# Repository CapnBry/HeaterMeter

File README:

This is the source code respository for the HeaterMeter and LinkMeter BBQ grill controllers. Documentation can be found in the wiki:
https://github.com/CapnBry/HeaterMeter/wiki

+-----+ +-----+ +------+
|Probe| |Probe| |Blower|
+-----+ +-----+ +------+
     |       |        |    2.5mm jacks
A +-------------+     |
V | HeaterMeter |-----/    (arduino/heatermeter)
R +-------------+
========|===============   Serial UART
  +------------------+
  | +------------+ |
O | | linkmeterd | |      (openwrt/package/linkmeter)
p | +------------+ |
e |       |        |      /var/run/linkmeter.sock
n |    +------+    |
W |    | luci |    |      LUA in-process
r |   +--------+   |
t |   | uhttpd |   |
  |   +--------+   |
  +-----------------+
  
Source Layout
3d/* - 3D printed parts source files
openwrt/* - Files you'd push to your router for LinkMeter
arduino/* - AVR source code for upload to your Arduino board
eagle/* - Hardware schematics and board files
pebble/* - Source to the Pebble app
tools/* - Miscellaneous scripts and .NET apps

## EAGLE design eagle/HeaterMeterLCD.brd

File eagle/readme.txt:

KiCad Files for HeaterMeter PCBs
Base - HeaterMeter Base Board (v4.3.5)
LCD - HeaterMeter v4.3 LCD and Button backpack board (v4.3.5)

-- Obsolete EAGLE files or of Limited Purpose --
HeaterMeterPI.brd / sch / png - HeaterMeter v4 board and schematic for standalone or RaspberryPi (up to v4.3.4)
HeaterMeterLCD.brd / sch / png - HeaterMeter v4.3 LCD and Button backpack board (up to v4.3.4)
RfAddon.brd / sch - HeaterMeter v4.2.4 RF addon board needed if lmremote / IT+ reception is desired
LMRemote.sch - Example RF Remote probe transmitter schematic (not used in v4.3)

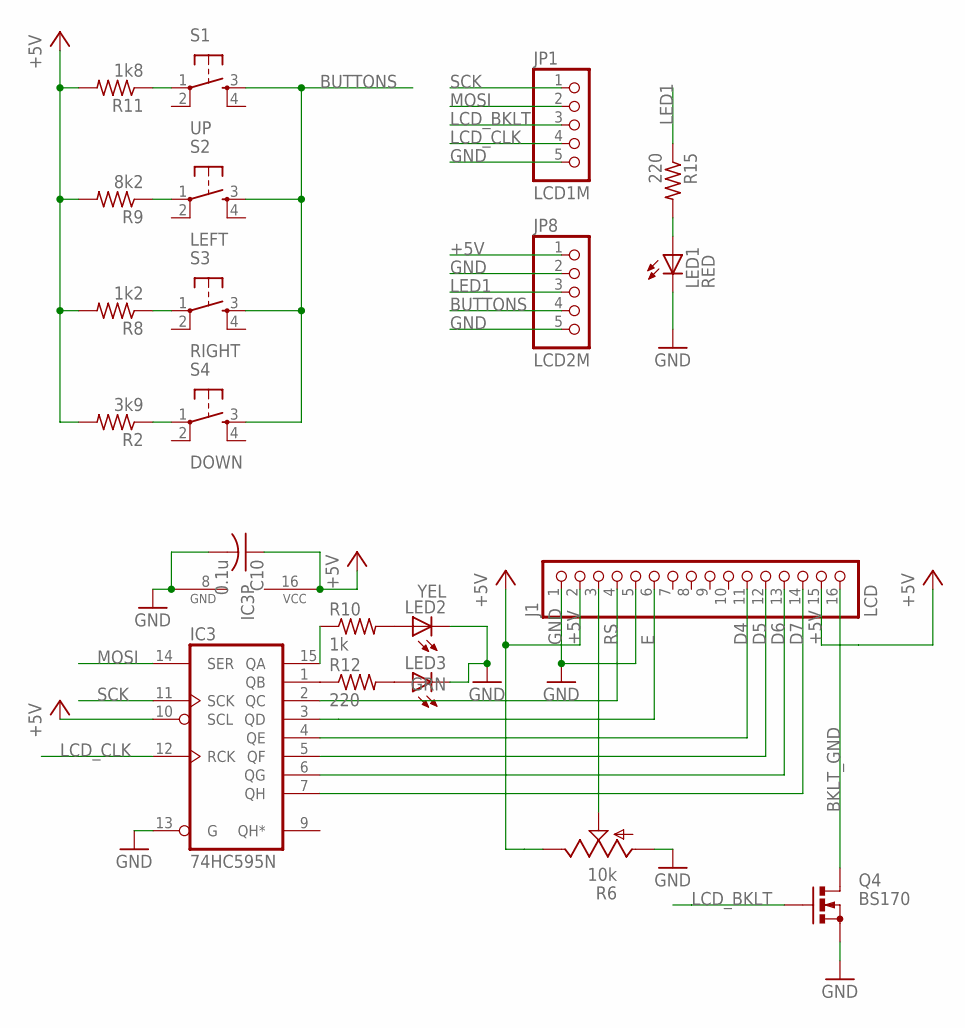
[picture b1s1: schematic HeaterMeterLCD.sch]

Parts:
C10: 0.1u; C025-025X050
IC3: 74HC595N; DIL16
J1: LCD; 1X16
JP1: LCD1M; 1X05
JP8: LCD2M; 1X05
LED1: RED; LED3MM
LED2: YEL; LED3MM
LED3: GRN; LED3MM
Q4: BS170; SOT54E
R2: 3k9; 0204/7
R6: 10k; POT-CT6-SIDE
R8: 1k2; 0204/7
R9: 8k2; 0204/7
R10: 1k; 0204/7
R11: 1k8; 0204/7
R12, R15: 220; 0204/7
S1: UP; TACT-OMRON-12MM
S2: LEFT; TACT-OMRON-12MM
S3: RIGHT; TACT-OMRON-12MM
S4: DOWN; TACT-OMRON-12MM

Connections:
+5V: C10.1, IC3.10 (SCL), IC3.16 (VCC), J1.2, J1.15, JP8.1, R2.2, R6.E, R8.2, R9.2, R11.2
BKLT_GND: J1.16, Q4.D
BUTTONS: JP8.4, S1.3, S2.3, S3.3, S4.3
D4: IC3.4 (QE), J1.11
D5: IC3.5 (QF), J1.12
D6: IC3.6 (QG), J1.13
D7: IC3.7 (QH), J1.14
E: IC3.3 (QD), J1.6
GND: C10.2, IC3.8 (GND), IC3.13 (G), J1.1, J1.5, JP1.5, JP8.2, JP8.5, LED1.K (C), LED2.K (C), LED3.K (C), Q4.S, R6.A
LCD_BKLT: JP1.3, Q4.G
LCD_CLK: IC3.12 (RCK), JP1.4
LED1: JP8.3, R15.1
MOSI: IC3.14 (SER), JP1.2
unnamed: R2.1, S4.1
unnamed: R11.1, S1.1
unnamed: J1.3, R6.S
unnamed: R9.1, S2.1
unnamed: LED2.A, R10.2
unnamed: LED1.A, R15.2
unnamed: R8.1, S3.1
unnamed: IC3.15 (QA), R10.1
unnamed: IC3.1 (QB), R12.1
unnamed: LED3.A, R12.2
RS: IC3.2 (QC), J1.4
SCK: IC3.11 (SCK), JP1.1

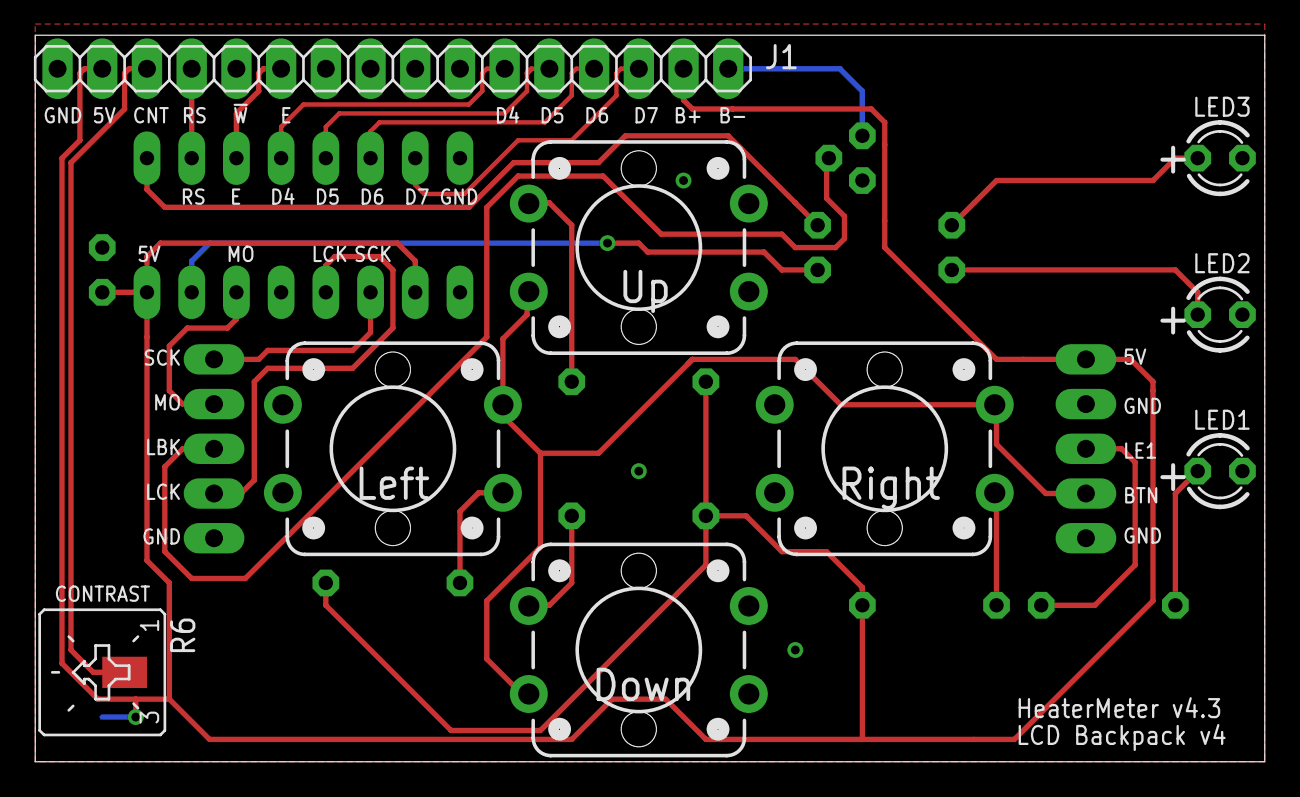
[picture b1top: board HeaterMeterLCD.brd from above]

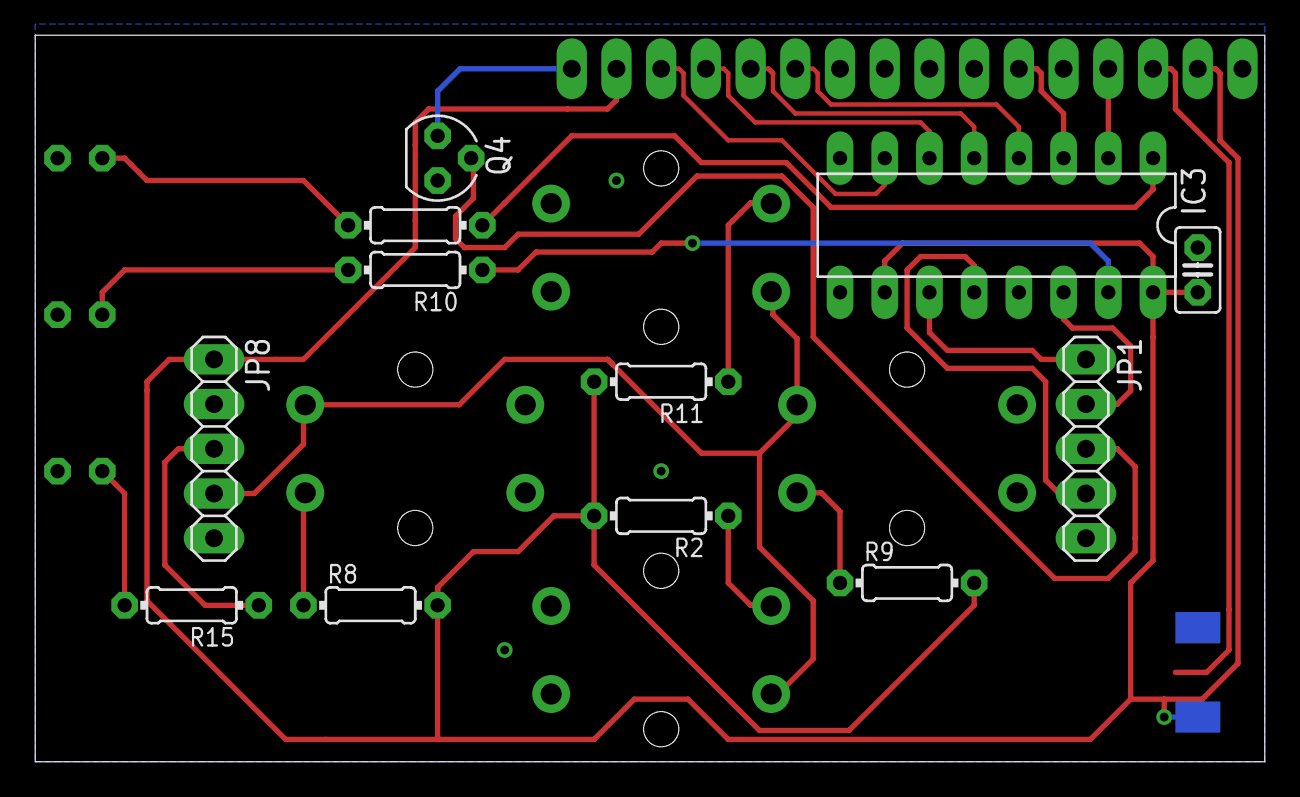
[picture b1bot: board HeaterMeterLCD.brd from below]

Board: 2 copper layers, 69.8 x 41.3 mm, 21 parts (12 on the bottom side), 25 nets.

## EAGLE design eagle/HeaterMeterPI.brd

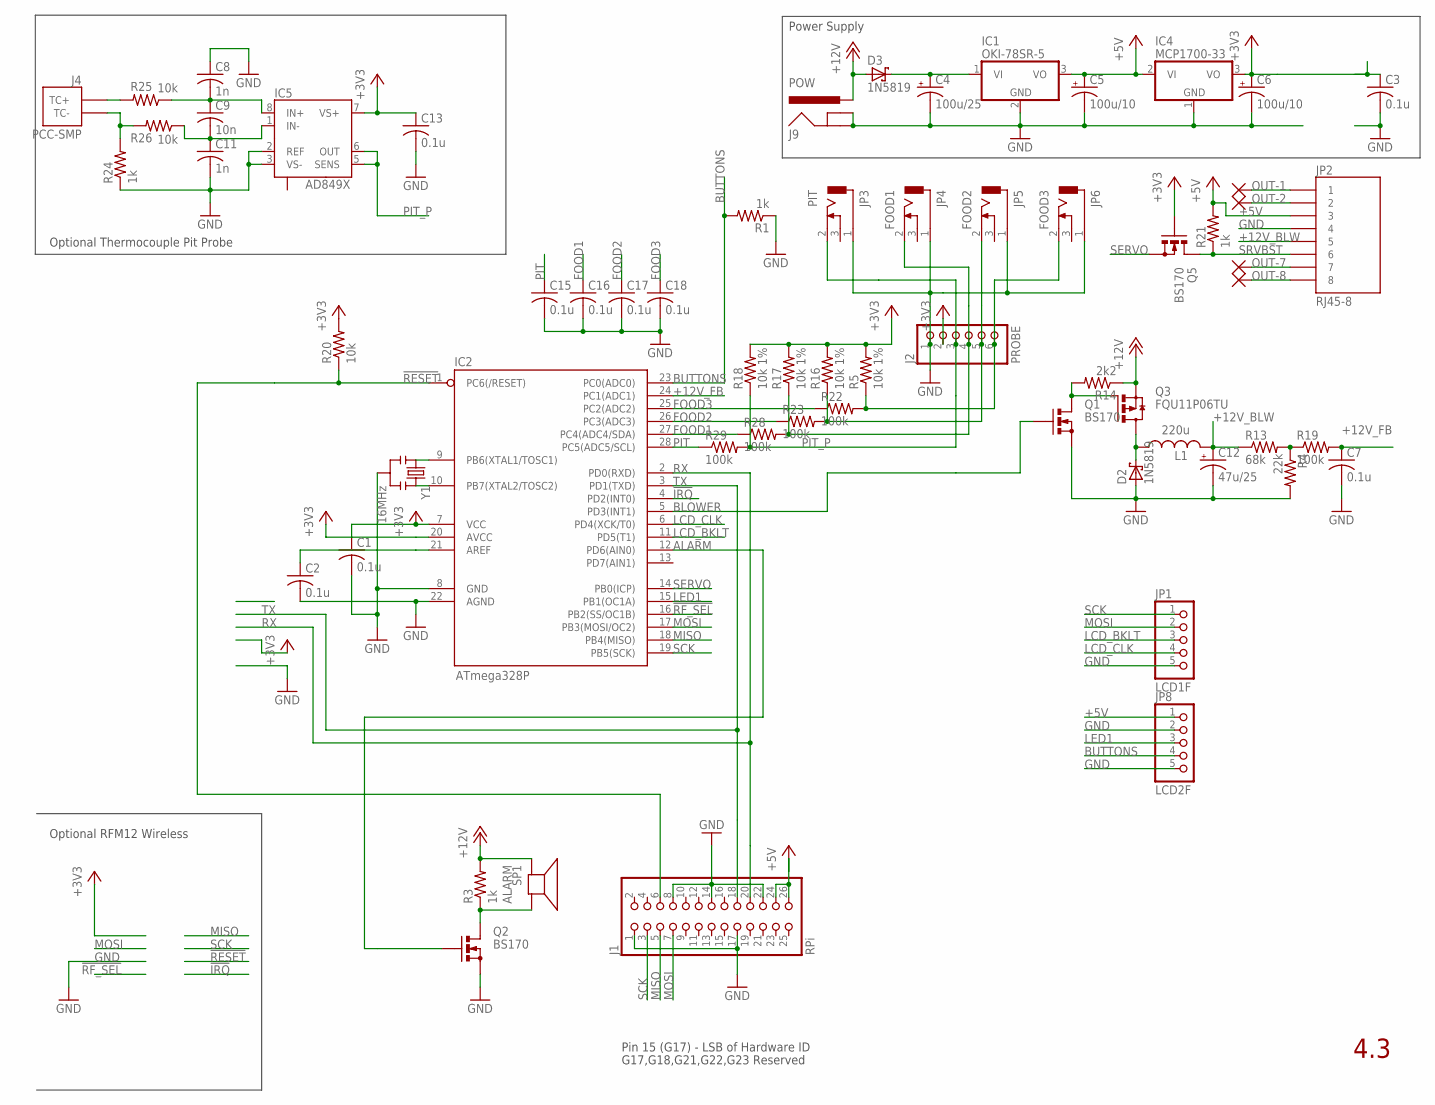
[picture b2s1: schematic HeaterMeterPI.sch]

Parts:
C1, C2, C3, C7, C15, C16, C17, C18: 0.1u; C025-025X050
C4: 100u/25; E2,5-6
C5, C6: 100u/10; E2,5-5
C8, C11: 1n; C0805
C9: 10n; C0805
C12: 47u/25; E2,5-5
C13: 0.1u; C0805
D2, D3: 1N5819; DO41-7
IC1: OKI-78SR-5; TO220HMURATA
IC2: ATmega328P; DIL28-3
IC4: MCP1700-33; TO92
IC5: AD849X; MSOP8
J1: RPi; 2X13
J2: PROBE; 1X06
J4: PCC-SMP
J9: POW; BARREL-2.1
JP1: LCD1F; 1X05
JP2: RJ45-8; RJ45-8-1H
JP3: PIT; CUI-MJ-2508
JP4: FOOD1; CUI-MJ-2508
JP5: FOOD2; CUI-MJ-2508
JP6: FOOD3; CUI-MJ-2508
JP8: LCD2F; 1X05
L1: 220u; E5-9
Q1, Q2, Q5: BS170; SOT54E
Q3: FQU11P06TU; TO251
R1, R3, R21: 1k; 0204/7
R4: 22k; 0204/7
R5, R16, R17, R18: 10k 1%; 0207/2V
R13: 68k; 0204/7
R14: 2k2; 0204/7
R19: 100k; 0204/7
R20: 10k; 0204/7
R22, R23, R28, R29: 100k; 0207/2V
R24: 1k; R0805
R25, R26: 10k; R0805
SP1: ALARM; AL11P
U$1, U$2, U$3, U$4: THROUGH-HOLE; PAD-032
Y1: 16MHz; RESONATOR-PTH

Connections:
!IRQ: IC2.4 (PD2(INT0))
!RESET: IC2.1 (PC6(/RESET)), J1.6, R20.1
!RF_SEL: IC2.16 (PB2(SS/OC1B))
+3V3: C1.1, C3.1, C6.+, C13.1, IC2.7 (VCC), IC2.20 (AVCC), IC4.3 (VO), IC5.7 (VS+), J2.2, Q5.G, R5.2, R16.2, R17.2, R18.2, R20.2
+5V: C5.+, IC1.3 (VO), IC4.2 (VI), J1.24, J1.26, JP2.3, JP8.1, R21.2
+12V: D3.A, J9.PWR, Q3.3 (S), R3.2, R14.1, SP1.+
+12V_BLW: C12.+, JP2.5, L1.NEG (2), R13.1
+12V_FB: C7.1, IC2.24 (PC1(ADC1)), R19.2
ALARM: IC2.12 (PD6(AIN0)), Q2.G
BLOWER: IC2.5 (PD3(INT1)), Q1.G
BUTTONS: IC2.23 (PC0(ADC0)), JP8.4, R1.2
FOOD1: C16.1, IC2.27 (PC4(ADC4/SDA)), R28.1
FOOD1_P: J2.4, JP4.2, R17.1, R28.2
FOOD2: C17.1, IC2.26 (PC3(ADC3)), R23.1
FOOD2_P: J2.5, JP5.2, R16.1, R23.2
FOOD3: C18.1, IC2.25 (PC2(ADC2)), R22.1
FOOD3_P: J2.6, JP6.2, R5.1, R22.2
GND: C1.2, C2.2, C3.2, C4.-, C5.-, C6.-, C7.2, C8.1, C11.2, C12.-, C13.2, C15.2, C16.2, C17.2, C18.2, D2.A, IC1.2 (GND), IC2.8 (GND), IC2.22 (AGND), IC4.1 (GND), IC5.2 (REF), IC5.3 (VS-), J1.1, J1.8, J1.14, J1.17, J1.22, J2.1, J9.GND, J9.GNDBREAK, JP1.5, JP2.4, JP3.1, JP4.1, JP5.1, JP6.1, JP8.2, JP8.5, Q1.S, Q2.S, R1.1, R4.2, R24.1, Y1.2
LCD_BKLT: IC2.11 (PD5(T1)), JP1.3
LCD_CLK: IC2.6 (PD4(XCK/T0)), JP1.4
LED1: IC2.15 (PB1(OC1A)), JP8.3
MISO: IC2.18 (PB4(MISO)), J1.5
MOSI: IC2.17 (PB3(MOSI/OC2)), J1.7, JP1.2
unnamed: Q1.D, Q3.1 (G), R14.2
unnamed: C2.1, IC2.21 (AREF)
unnamed: D2.C, L1.POS (1), Q3.2@1 (D), Q3.2@2 (D)
unnamed: R4.1, R13.2, R19.1
unnamed: Q2.D, R3.1, SP1.-
unnamed: IC2.10 (PB7(XTAL2/TOSC2)), Y1.3
unnamed: IC2.9 (PB6(XTAL1/TOSC1)), Y1.1
unnamed: J4.TC+, R25.2
unnamed: J4.TC-, R24.2, R26.2
OUT-1: JP2.1, U$3.P
OUT-2: JP2.2, U$4.P
OUT-7: JP2.7, U$2.P
OUT-8: JP2.8, U$1.P
PIT: C15.1, IC2.28 (PC5(ADC5/SCL)), R29.1
PIT_P: IC5.5 (SENS), IC5.6 (OUT), J2.3, JP3.2, R18.1, R29.2
RX: IC2.2 (PD0(RXD)), J1.20
SCK: IC2.19 (PB5(SCK)), J1.3, JP1.1
SERVO: IC2.14 (PB0(ICP)), Q5.S
SRVBST: JP2.6, Q5.D, R21.1
TC+: C8.2, C9.1, IC5.8 (IN+), R25.1
TC-: C9.2, C11.1, IC5.1 (IN-), R26.1
TX: IC2.3 (PD1(TXD)), J1.18
VRM_IN: C4.+, D3.C, IC1.1 (VI)

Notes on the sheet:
Optional RFM12 Wireless
Power Supply
4.3
Optional Thermocouple Pit Probe
Pin 15 (G17) - LSB of Hardware ID
G17,G18,G21,G22,G23 Reserved

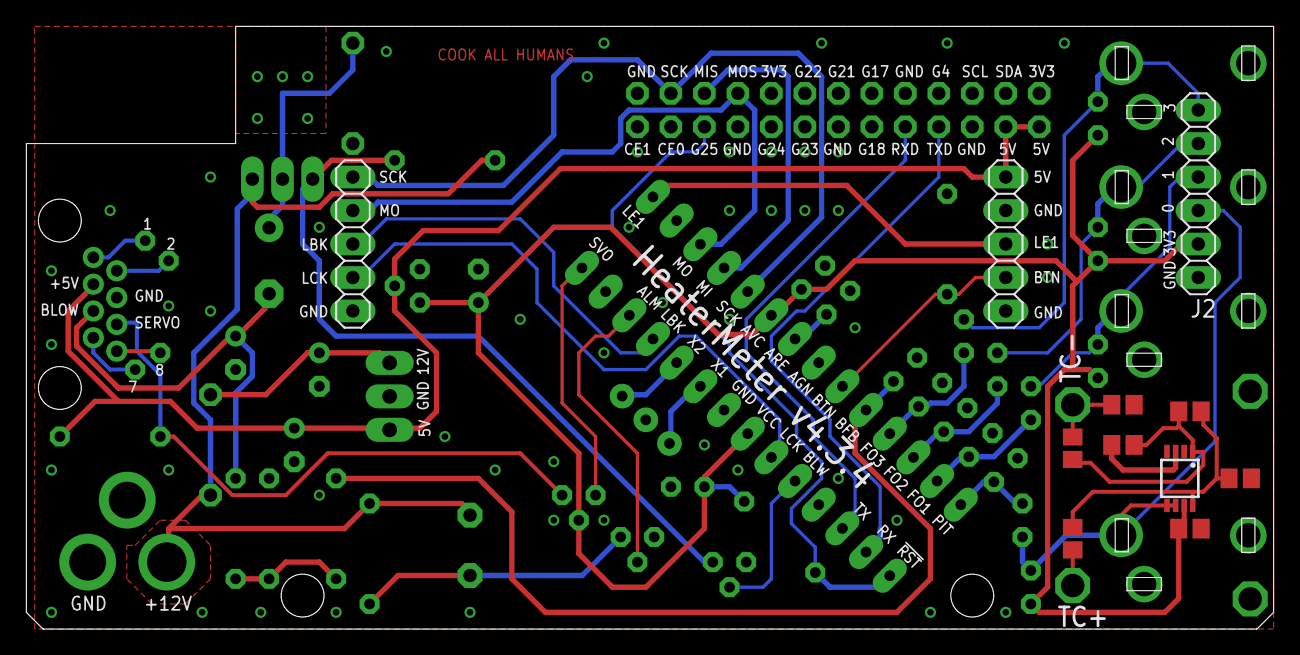
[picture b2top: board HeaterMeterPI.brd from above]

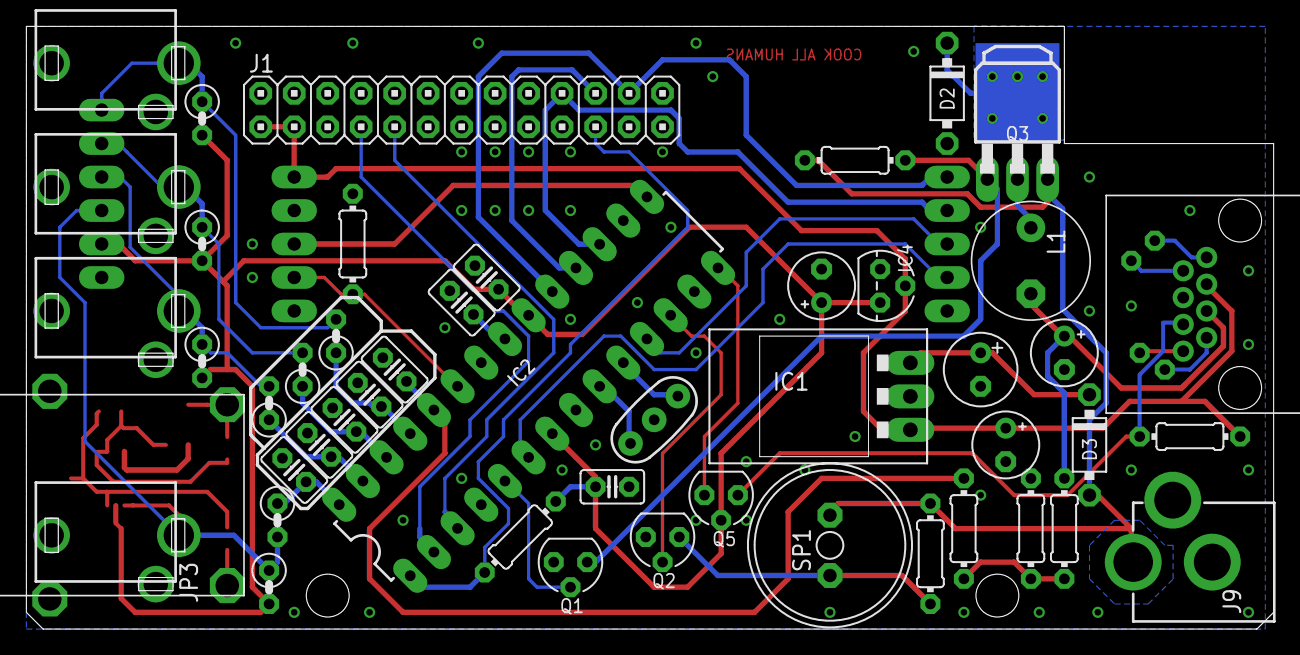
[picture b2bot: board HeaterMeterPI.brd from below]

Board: 2 copper layers, 94.6 x 45.7 mm, 63 parts (48 on the bottom side), 44 nets.

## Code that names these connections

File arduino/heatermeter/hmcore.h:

// HeaterMeter Copyright 2019 Bryan Mayland <bmayland@capnbry.net>
#ifndef __HMCORE_H__
#define __HMCORE_H__

#include "strings.h"

#define HEATERMETER_SERIAL 38400 // enable serial interface
#define HEATERMETER_RFM12  RF12_915MHZ  // enable RFM12B receiving (433MHZ|868MHZ|915MHZ)
#define PIEZO_HZ 4000             // enable piezo buzzer at this frequency
#if HM_BOARD_REV == 'A'
#define SHIFTREGLCD_NATIVE        // Use the native shift register instead of SPI (HM PCB <v3.2)
#endif

#include "ShiftRegLCD.h"
#include "serialxor.h"
#include "grillpid.h"
#include "hmmenus.h"

// Analog Pins
// Number in the comment is physical pin on ATMega328
#define PIN_PIT     5       // 28
#define PIN_FOOD1   4       // 27
#define PIN_FOOD2   3       // 26
#define PIN_AMB     2       // 25
//#define PIN_FFEEDBACK 1     // 24 (grillpid_conf.h)
#define PIN_BUTTONS 0       // 23
// Digital Output Pins
#define PIN_SERIALRX     0  // 2 Can not be changed
#define PIN_SERIALTX     1  // 3 Can not be changed
#define PIN_INTERRUPT    2  // 4
//#define PIN_BLOWER       3  // 5 (grillpid_conf.h)
#define PIN_LCD_CLK      4  // 6
#define PIN_LCD_BACKLGHT 5  // 11
//#define PIN_ALARM        6  // 12 (tone_4khz.h)
//#define PIN_SOFTRESET    7  // 13 DataFlash SS on WiShield, no longer used for reset
//#define PIN_SERVO        8  // 14 LCD_DATA on < HM PCB v3.2 (grillpid_conf.h)
#define PIN_WIRELESS_LED 9  // 15
#if !defined(PIN_SPI_SS)
#define PIN_SPI_SS      10  // 16
#define PIN_SPI_MOSI    11  // 17 Can not be changed
#define PIN_SPI_MISO    12  // 18 Can not be changed
#define PIN_SPI_SCK     13  // 19 Can not be changed
#endif

void hmcoreSetup(void);
void hmcoreLoop(void);

void eepromLoadConfig(unsigned char forceDefault);
void storePidMode();
void storeSetPoint(int sp);
void loadProbeName(unsigned char probeIndex);
void storeAndReportProbeOffset(unsigned char probeIndex, int offset);
void storeAndReportMaxFanSpeed(unsigned char maxFanSpeed);
void storeLcdBacklight(unsigned char lcdBacklight);
void reportLcdParameters(void);
void Debug_begin(void);
void publishLeds(void);
#define Debug_end Serial_nl
void silenceRingingAlarm(void);

#define LIDPARAM_OFFSET 0
#define LIDPARAM_DURATION 1
#define LIDPARAM_ACTIVE 2
void storeLidParam(unsigned char idx, int val);

extern GrillPid pid;
extern ShiftRegLCD lcd;

#endif /* __HMCORE_H__ */

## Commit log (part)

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2016-09-30 [wrt] Fix parted compilation
2016-09-30 [wrt] Remove spi-bcm2708, now included in platform modules.mk
2016-09-30 [wrt] Update from url patch updated to trunk luci
2016-09-30 [wrt] Remove dnsmasq add hostname
    Trunk now properly adds ipv4 and ipv6 hostname for "lan" network by default
2016-09-30 [wrt] Update luci-app-msmtp to 1.6.2 and match new luci base
2016-09-30 [lm] Allow use of 'auto' serial port, and make baud default to 38400 if not present
2016-09-30 [wrt] Refresh bcm2708 tweaks for Designated Driver and RPi 3
2016-09-30 [lm] Updated coefficients for Thermoworks ProSeries (0.4C-1.1C increase from 25C-150C)
2016-09-30 [wrt] Add 'reset config' to sysupgrade-url (now flashops) patch
2016-09-30 [lm] Updates for OpenWrt Designated Driver / Pi 3
    -- Linkmeter now uses its own config file instead of lucid
    -- Linkmeter is standaone, no longer requires lucid host process
    -- Still much to do but up and running
2016-10-01 [wrt] Simplify luci-app-msmtp Makefile to use luci.mk
2016-10-01 [wrt] LinkMeter depends on luci-base instad of luci, allows removal of firewall packages
2016-10-05 [3d] Remove mousears, add configurable body chamfer and walls now full 3mm
2016-10-11 [3d] USB pillars fix for interferrence with Pi PCB, locklip_p thickness increase, others
    -- Pi PCB was interferring with the USB pillar reinforcements on the
    bottom
    -- Increase locklip_p bar thickness to WALL to allow a more solid fill
    -- Reduce top negative body inset chamfer, this didn't seem to make any
    difference in warping and takes longer / more material to print.
    -- Add vertical internal body corner fillets to the top two corners to
2016-10-20 [lm] Use #content background color for png graph
2016-10-20 [lm] 20161018B firmware
2016-11-17 [3d] Increase effective nut ingress width, locklip_p has inset, LCD block taper
    -- Nut ingress is now a sideways trapezoid so it starts wider and tapers
    in.
    -- Ingress width lowered 5.8->5.7mm
    -- Nut recess no longer offset 0.4mm, elongated the points 0.2mm each
    side
    -- Locklip_p now default inset is 0, only the insert is inset now to
2016-11-24 [3d] Reduce the size of the Pi right edge stop -0.5mm
    It makes the case a little more difficult to assemble if the Pi jams up
    on it
2016-12-22 [3d] Add a heatshield option to help trap heat
2016-12-26 [hm] Fix WDT not disabling on gcc-4.9.2 (Atmel 3.5.3)
    .init3 section was not being included after Arduino 1.6.10. Much thanks
    to Andrew Fuller for discovering the GCC -flto cause.
2016-12-30 [lm] Remove old lucid restart on install / uninstall
2016-12-30 [wrt] No longer generate pi3 images with kernel7, remove HDMI forced resolution
2017-03-21 [wrt] Update add hostname patch for compatibility with latest udhcpc
2017-04-05 [lm] Update LinkMeter to support Zero W, LEDE
2017-04-07 [lm] Move the network address checking to a plugin
2017-04-09 [3D] Add probewrap probe spool model
2017-04-09 Ignore stl files in the 3D directory
2017-04-11 [3d] Probe centerline moved up 0.3mm by math
    2.25 - mount support
    1.5? - Pi PCB thickness
    2.54 - male header black bit
    8.5 - female header
    -5.5 - probe jack
    = 9.29mm
2017-04-13 [lm] Add beginning of official REST API
2017-04-16 [hm] HeaterMeter 20170415 22,324 bytes
2017-04-16 [3d] Pi mounting screw location now based on position from front wall instead of back
2017-04-16 [lm] HeaterMeter 20170415
2017-05-09 [wrt] Include ca-certificates as MSMTP trust file
2017-05-13 [wrt] Update to latest LEDE (Linux 4.9.20)
2017-06-28 [lm] Add /lm/api/fw API endpoint
2017-07-10 [wrt] Enable USB mass storage, umdns, uhttpd-mod-lua needed for already comitted features
2017-07-11 [lm] Add wifi page to linkmeter webui for quick wifi client setup
2017-07-16 [lm] Hide key field if Open encryption selected
2017-07-16 [lm] Hooray, procd_add_mdns only supports a single service
2017-07-22 [3d] Ignore gcode files too
2017-07-22 [3d] Refactor to not use rotate_extrude(angle)
2017-07-22 [hm] Fix not able to disable alarm by pressing device button
    Thanks Kiaikai B for reporting
2017-07-23 Change REMOTE_BASE to use https
2017-07-24 [www] Make AVR firmware repository URL protocol relative. Fixes #38
    Thanks Steve M!
2017-07-30 [hm] pid.setDisabled(true) now forces return to auto mode
2017-07-30 [lm] Snapshot current HM configuration when doing a stash
    The configuration is stored in a json-formatted text file along side the stashdb. If present,
    the webui will display the json's stash.desc string on the list.
    Backups will now include these json files and they will be deleted if the stash rrd is deleted.
2017-08-22 [wrt] Switch from rtl8xxxu to rtl8192cu driver, enable uhttpd-lua
2017-08-28 [lm] Convert linkmeterd config reset to use squashfs
2017-08-30 [3d] Increase front offset 0.8->1.0, move probes back 0.6mm, decrease pic_ex 2->1.7
2017-09-26 [lm] Hide bogus error about missing default-config.tar.gz on startup
2017-10-06 [lm] Configure SMTP client to use heatermeter.com if no server is configured on install
2017-10-11 [lm] 20170916B firmware
2017-11-06 [ssdp] Recreate ssdp socket if IP_ADD_MEMBERSHIP fails, don't just crash
    The interface list changes but the socket is closed, so check every 10 seconds
    a new socket needs to be created.
    Also force a NOTIFY one second after startup rather than waiting the full timeout.
2017-12-13 [hm] Don't hang indefinitely on init if there's no RF12 module
2017-12-30 [hm] fix links for pushbullet and pushover
2018-01-08 [wrt] Add exFAT support and switch back to rtl8xxxx wifi
2018-01-24 [wrt] Prevent bogus firmware download when flashing from uploaded file
2018-03-22 [wrt] Update patches for Pi3 Plus
2018-03-27 [wrt] Fix SSDP multicast join/rejoin happening too frequently
2018-04-05 [3d] Move probe jacks back to calculated position, pi connector fix for v.thick walls
    Seems that maybe the probe jacks were 0.6mm too far forward? Also the Pi
    connectors wouldn't poke all the way through with a wall thickness of
    0.25"
2018-04-05 [hm] Immediately update the status LEDs when using the buttons to enter/exit lid mode for faster feedback
2018-06-07 [hm] Add thermocouple non-linearity compensation
    Uses Table 3 from Analog Devices's AN-1087.
    0C-320C only. Subtract up to 1.0C at 140C and add 1.01C at 260C.
2018-08-08 [eagle] LCD backpack v4
    -- Remove solder mask on edges of LED GND pins
    -- Enlarge pot pin width 0.05 -> 0.07
    -- Silence schematic warning about 5V pin overlap
2018-08-19 Fixed inconsistent naming that prevented api to add CORS header
2018-11-29 [3d] Case LCD pins cutout isn't needed
    The LCD pins aren't even as long as the shift register pins are!
2018-12-31 [lm] Fixed inconsistent naming that prevented api to add CORS header
    Thanks Robert Spari for reporting and fixing
2018-12-31 [lm] Fix API access not working at all since LuCI changes
2019-03-28 Exclude Slic3r .3mf files
2019-03-29 [hm] Fix typo that broke compile
2019-04-18 [hm] Fix LCD backlight visually resetting when being changed through the menu
2019-06-18 [3d] Add option for mouselegs
2019-07-26 [lm/www] RRD now stores down to -200, webui conf allow offsets up to 4 digits
2019-10-09 Update copyright year to 2019
2019-12-26 [hm] Add .vs directory to .gitignore
2020-01-07 [www] Add N keybinding to home page to turn on noise graph
2020-01-07 [www] Fix HTML error in credits page
2020-01-20 [hm] Report noisedump one cycle after pin number is set to imrpove response time
2020-02-09 [www] Fix graph tooltip appearing under Fan speed in Output bar
2020-02-09 [www] Spread noisegraph across the whole graph area for users who arent logged in
2020-02-14 [www] Add link to Light home page to the home page
2020-02-15 [www] Fix improper probe colors in archive view
2020-03-14 Abort to usage() if target is unknown because I keep trying BRCM2708
2020-04-01 [hm] Allow servo ranges to be reversed
2020-04-01 [hm] Get back to Unix (LF) line endings
2020-07-15 [3d] Make end piece snap hole slightly undersized for a tighter fit
2020-07-15 [3d] Add simple plate Big Green Egg fan adapter
2020-07-23 [www] Add QRCode popup for apikey to conf page
2020-08-03 [lm/www] Change Ramp Mode to use one or more probes averaged together
2020-08-19 [3d] Change LED holes to be small pillars
2020-10-09 [www] Add parsing support for differential noisedump event and string
2020-10-09 [lm] Add hmlive device registration result to NETINFO menu
2020-11-17 [hm] Include units in HMPD, remove pidb reporting (zeroed out)
2020-11-20 [hm] Report the PID units when changed via HMPC
2020-11-20 [lm] Reset entire peak tracking state if the pit probe is unplugged
2020-11-23 [lm] Add linkmeter.daemon.serial_log option for setting the path to and enabling serial logging
2020-12-18 [www] Add a suggestion for longer lid duration to config page
2020-12-23 [www] Add rename support to stash page
2020-12-29 [www] Code cleanup, all var replaced with let on home page
2021-01-14 [hm] 20201220 version string
2021-02-01 [hmc] Adding HeaterMeterClient Arduino library
2021-02-04 [mm] Add wiring to README
2021-02-05 [hmc] Add automatic host discovery
2021-02-16 [mm] Fix wrong pin for Probe3 in README
2021-02-19 [mm] Remove TaskScheduler library and update readme with library requirements
2021-02-23 [hmc] Add pidint event support
2021-02-24 [smushi] Add SMUSHI project
2021-02-25 [smushi] Paint optimization, button swaps, sleep mode
    -- Only paint Output and Setpoint boxes if data has changed
    -- Move ROTATE to left button, hold down to enter Power Down mode (<1mA)
    -- Have to hold right button now to use compiled wifi credentials
    will use last credentials otherwise
2021-05-24 [hmc] Add idle timeout message
2021-05-24 [hmc] Use 32bit time_t
    The update time is actually UNIX epoch and the time_t
    is 64-bit in ESP8266 3.0.0 so arduinojson was erroring.
2021-06-25 [hmc] UNIX time is signed not unsigned
2021-09-23 [3d] Increase led_fudge 0.3 -> 0.4
